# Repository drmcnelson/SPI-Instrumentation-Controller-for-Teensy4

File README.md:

# SPI Instrumentation Controller using Teensy 4.0

Controller board for the SPI Instrumentation project, hosts a Teensy 4.0 and provides connectors for SPI, instrumentation control, 3.3V and 5V power, a precision voltage references, dedicated pins for trigger and gate input, sync and busy output and a set of pins that can be used for analog input or digital i/o.   The connectors are identified in images below.

## Connectors

The following shows the location of the pins for the SPI interface circled in red.

The following shows the location of the pins for interfacing to the Linear CCD SPI boards, circled in red.

The following shows the location of the pins for trigger and gate input and sync and busy output, circled in red.

## Example use
Here is an example of how the board is used, the other two boards in this picture are the InAmp and +5V,-5V power supply.

## Obtaining boards

This repo includes files for FAB and assembly. 

You can [order assembled boards from PCBWAY here](https://www.pcbway.com/project/shareproject/Controller_Teensy_4_0_for_SPI_Instrumentation_boards_4b27edb1.html).

To assemble the board yourself you will need a reflow oven.  You can order bare boards from a sevice such as PCBWay or AllPCB, and use the BOM spreadsheet file to order parts from Digikey

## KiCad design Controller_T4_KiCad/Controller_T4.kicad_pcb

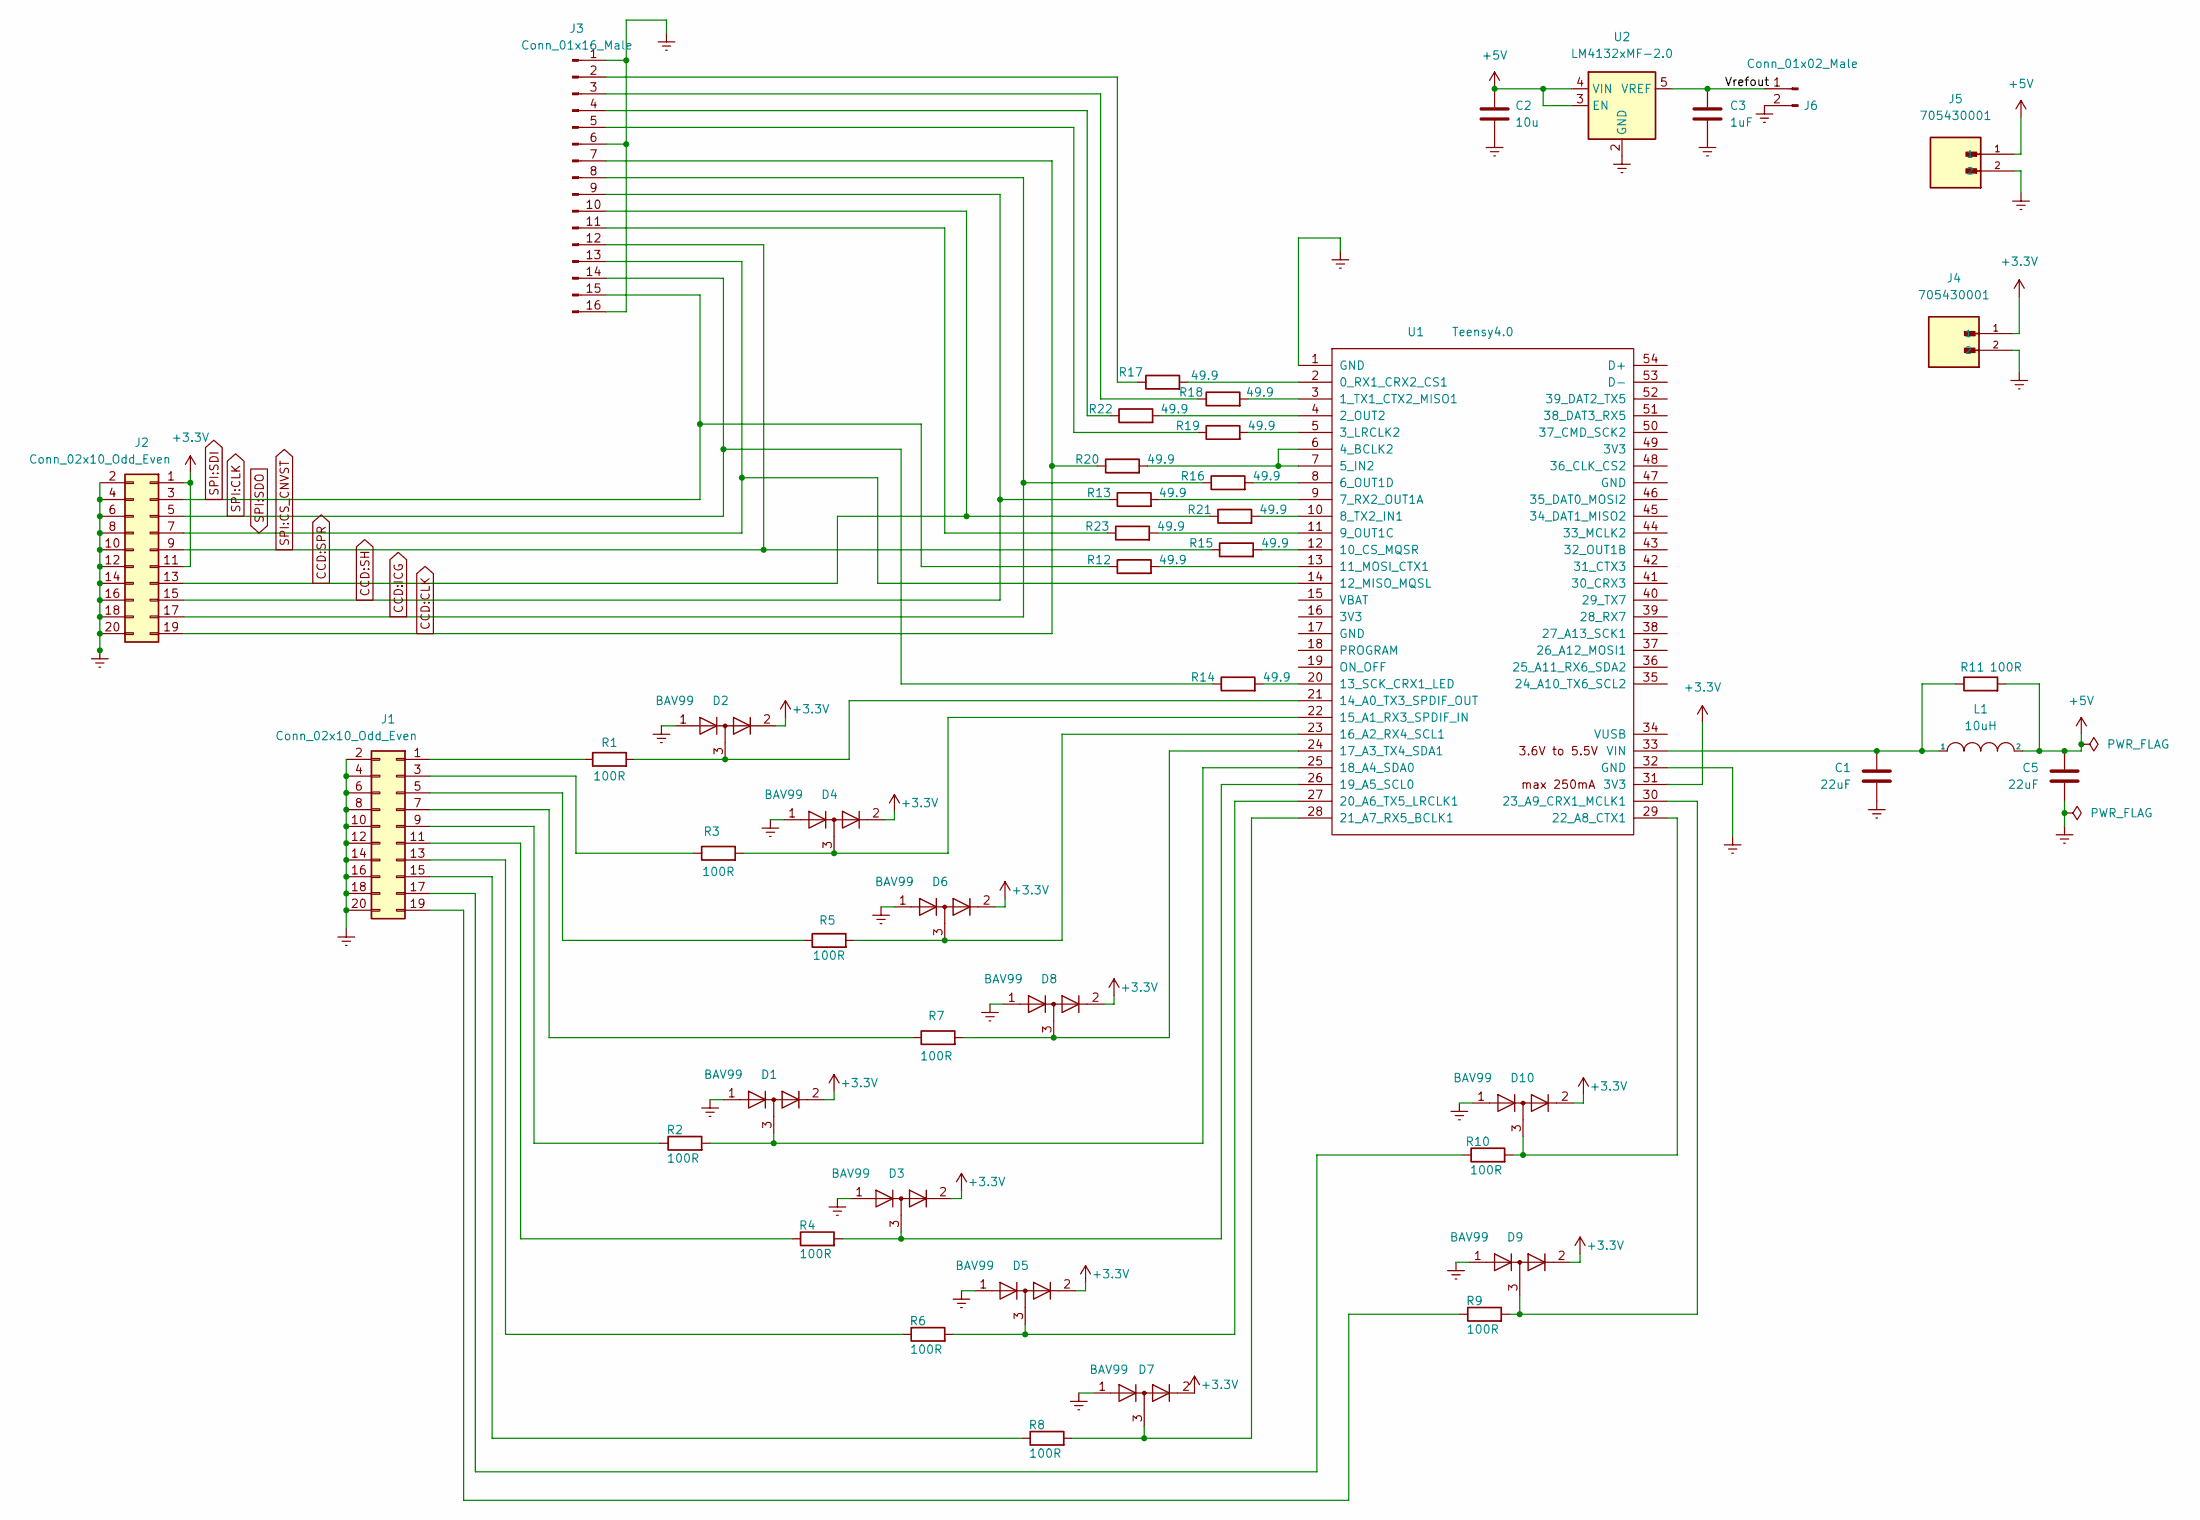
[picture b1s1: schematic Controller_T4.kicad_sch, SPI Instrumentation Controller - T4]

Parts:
C1, C5: 22uF; C_0805_2012Metric; Digikey 490-12389-1-ND
C2: 10u; C_0603_1608Metric_Pad1.08x0.95mm_HandSolder; Digikey 490-12317-1-ND
C3: 1uF; C_0603_1608Metric_Pad1.08x0.95mm_HandSolder; Digikey 1276-1034-1-ND
D1, D2, D3, D4, D5, D6, D7, D8, D9, D10: BAV99; SOT-23; Digikey 1727-2914-1-ND
J1, J2: Conn_02x10_Odd_Even; PinHeader_2x10_P2.54mm_Vertical; Digikey 3M156308-20-ND
J3: Conn_01x16_Male; PinHeader_1x16_P2.54mm_Vertical; Digikey 3M156268-16-ND
J4, J5: 705430001; MOLEX_705430001; PARTREV M1; Digikey WM4800-ND
J6: Conn_01x02_Male; PinHeader_1x02_P2.54mm_Vertical; Digikey 3M156268-02-ND
L1: 10uH; L_Taiyo-Yuden_NR-40xx; Digikey 587-2886-1-ND
R1, R2, R3, R4, R5, R6, R7, R8, R9, R10, R11: 100R; R_0603_1608Metric; Digikey 10-ERJ-UP3F1000VCT-ND
R12, R13, R14, R15, R16, R17, R18, R19, R20, R21, R22, R23: 49.9; R_0603_1608Metric; Digikey RMCF0603FT49R9CT-ND
U1: Teensy4.0; Teensy40; Digikey 1568-DEV-16997-ND
U2: LM4132xMF-2.0; SOT-23-5; Digikey LM4132BMF-2.0/NOPBCT-ND

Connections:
+3.3V: D1.2 (A), D2.2 (A), D3.2 (A), D4.2 (A), D5.2 (A), D6.2 (A), D7.2 (A), D8.2 (A), D9.2 (A), D10.2 (A), J2.1, J2.11, J4.1, U1.31 (3V3)
+5V: C2.1, C5.1, J5.1, L1.2, R11.2, U2.3 (EN), U2.4 (VIN)
/Vrefout: C3.1, J6.1, U2.5 (VREF)
CCD:CLK: J2.19, J3.7, R20.1
CCD:ICG: J2.17, J3.8, R16.1
CCD:SH: J2.15, J3.9, R13.1
CCD:SPR: J2.13, J3.10, R21.1
Earth: C1.2, C2.2, C3.2, C5.2, D1.1 (K), D2.1 (K), D3.1 (K), D4.1 (K), D5.1 (K), D6.1 (K), D7.1 (K), D8.1 (K), D9.1 (K), D10.1 (K), J1.2, J1.4, J1.6, J1.8, J1.10, J1.12, J1.14, J1.16, J1.18, J1.20, J2.2, J2.4, J2.6, J2.8, J2.10, J2.12, J2.14, J2.16, J2.18, J2.20, J3.1, J3.6, J3.16, J4.2, J5.2, J6.2, U1.1 (GND), U1.32 (GND), U2.2 (GND)
unnamed: C1.1, L1.1, R11.1, U1.33 (VIN)
unnamed: D1.3 (K), R2.2, U1.25 (18_A4_SDA0)
unnamed: D2.3 (K), R1.2, U1.21 (14_A0_TX3_SPDIF_OUT)
unnamed: D3.3 (K), R4.2, U1.26 (19_A5_SCL0)
unnamed: D4.3 (K), R3.2, U1.22 (15_A1_RX3_SPDIF_IN)
unnamed: D5.3 (K), R6.2, U1.27 (20_A6_TX5_LRCLK1)
unnamed: D6.3 (K), R5.2, U1.23 (16_A2_RX4_SCL1)
unnamed: D7.3 (K), R8.2, U1.28 (21_A7_RX5_BCLK1)
unnamed: D8.3 (K), R7.2, U1.24 (17_A3_TX4_SDA1)
unnamed: D9.3 (K), R9.2, U1.30 (23_A9_CRX1_MCLK1)
unnamed: D10.3 (K), R10.2, U1.29 (22_A8_CTX1)
unnamed: J1.1, R1.1
unnamed: J1.3, R3.1
unnamed: J1.5, R5.1
unnamed: J1.7, R7.1
unnamed: J1.9, R2.1
unnamed: J1.11, R4.1
unnamed: J1.13, R6.1
unnamed: J1.15, R8.1
unnamed: J1.17, R10.1
unnamed: J1.19, R9.1
unnamed: J3.2, R17.1
unnamed: J3.3, R18.1
unnamed: J3.4, R22.1
unnamed: J3.5, R19.1
unnamed: J3.11, R23.1
unnamed: R12.2, U1.13 (11_MOSI_CTX1)
unnamed: R13.2, U1.9 (7_RX2_OUT1A)
unnamed: R14.2, U1.20 (13_SCK_CRX1_LED)
unnamed: R15.2, U1.12 (10_CS_MQSR)
unnamed: R16.2, U1.8 (6_OUT1D)
unnamed: R17.2, U1.2 (0_RX1_CRX2_CS1)
unnamed: R18.2, U1.3 (1_TX1_CTX2_MISO1)
unnamed: R19.2, U1.5 (3_LRCLK2)
unnamed: R20.2, U1.6 (4_BCLK2), U1.7 (5_IN2)
unnamed: R21.2, U1.10 (8_TX2_IN1)
unnamed: R22.2, U1.4 (2_OUT2)
unnamed: R23.2, U1.11 (9_OUT1C)
SPI:CLK: J2.5, J3.14, R14.1
SPI:CS_CNVST: J2.9, J3.12, R15.1
SPI:SDI: J2.3, J3.15, R12.1
SPI:SDO: J2.7, J3.13, U1.14 (12_MISO_MQSL)

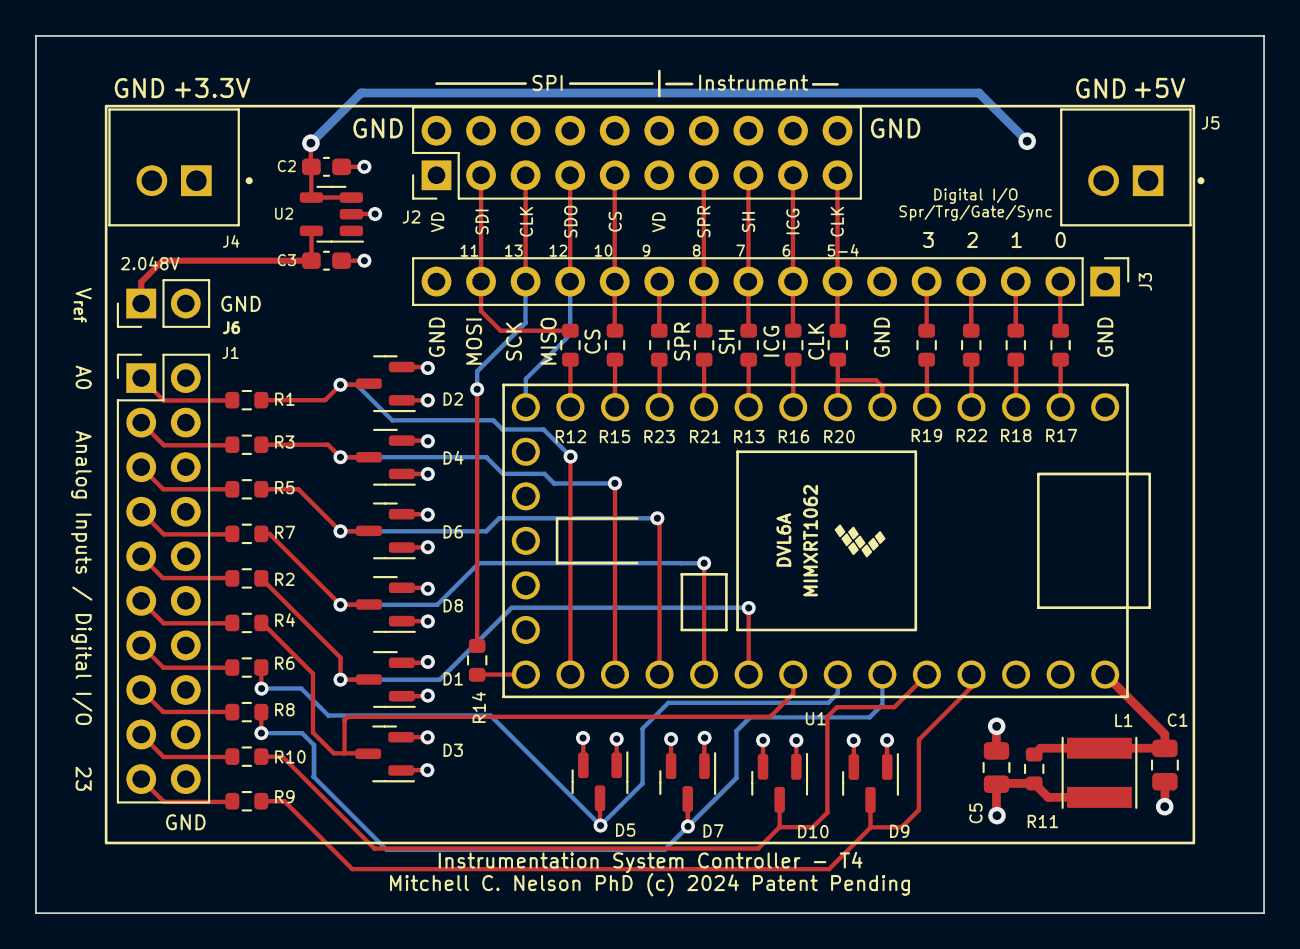
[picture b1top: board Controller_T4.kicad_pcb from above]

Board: 4 copper layers, 70.0 x 50.0 mm, 46 parts (0 on the bottom side), 50 nets.

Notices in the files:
Controller_T4_KiCad/Controller_T4.kicad_pcb:
Mitchell C. Nelson PhD (c) 2024 Patent Pending
Controller_T4_KiCad/Controller_T4.kicad_sch:
Mitchell C Nelson, PhD (c) 2023
